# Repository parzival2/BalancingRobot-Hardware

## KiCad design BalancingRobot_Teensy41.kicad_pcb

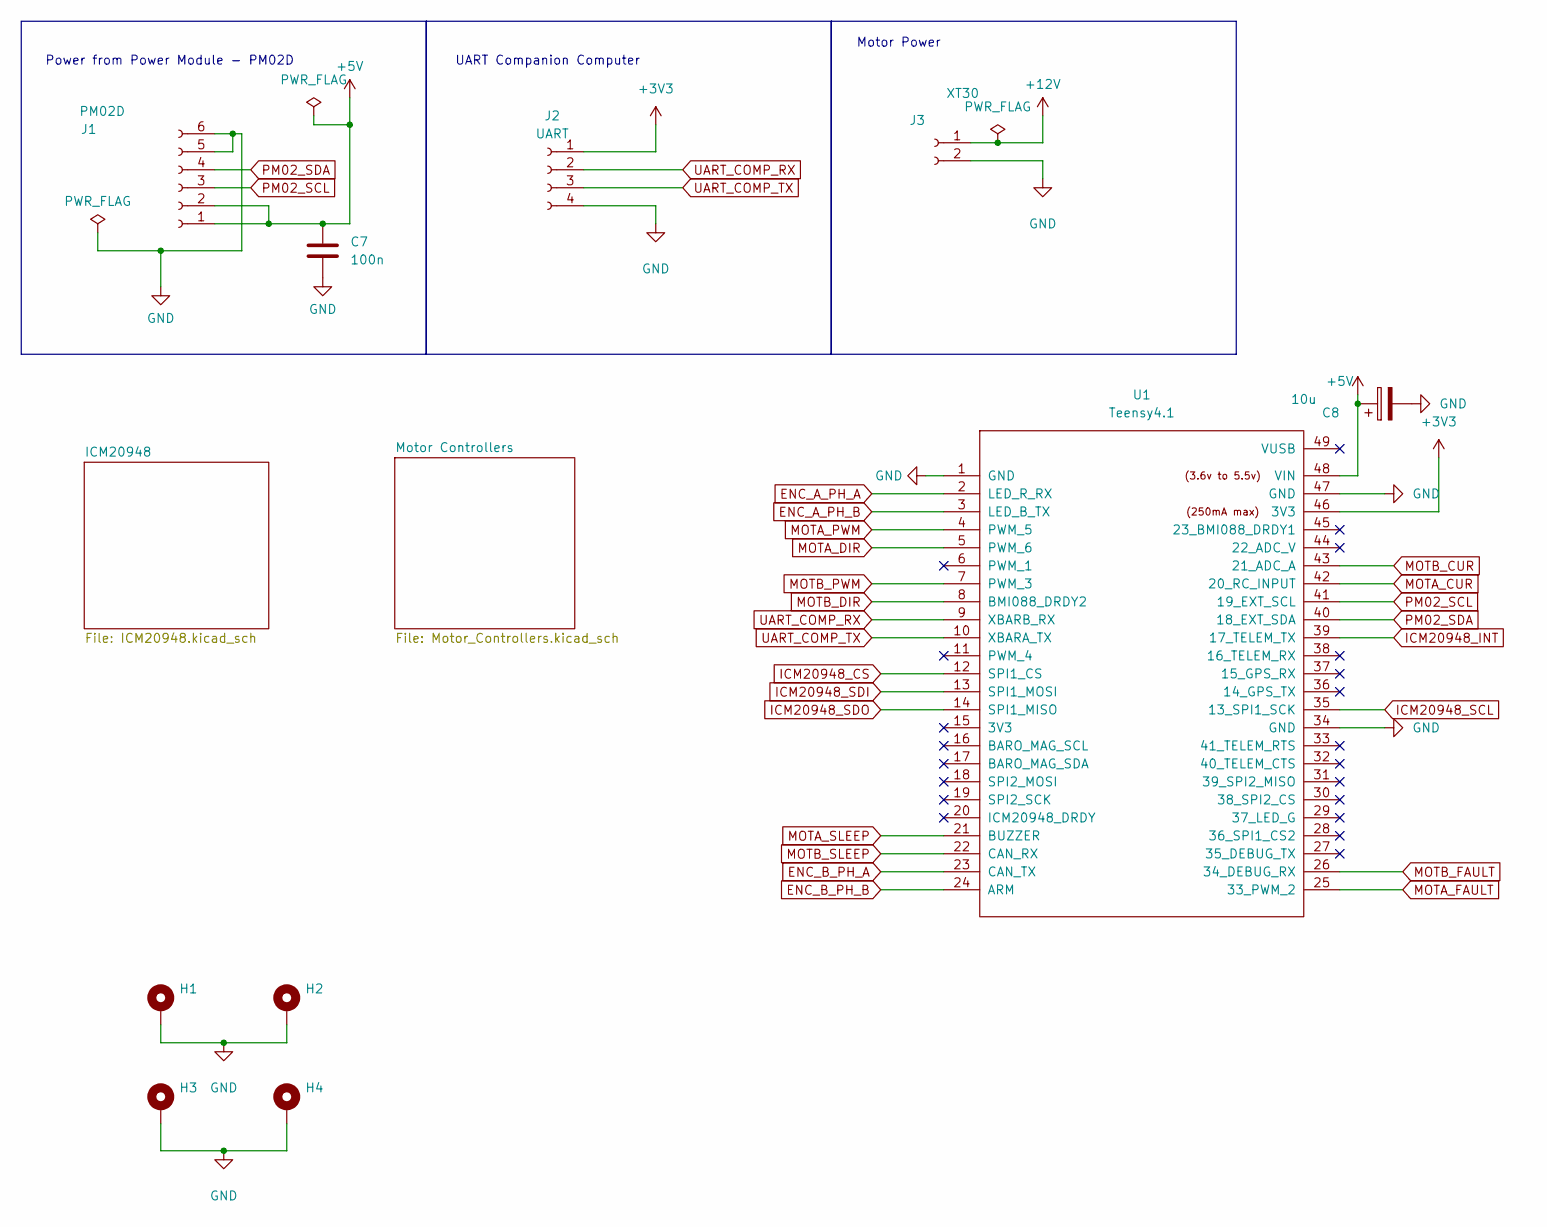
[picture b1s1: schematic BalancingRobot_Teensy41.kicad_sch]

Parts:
C7: 100n; C_Disc_D5.0mm_W2.5mm_P5.00mm
C8: 10u; CP_Radial_D5.0mm_P2.50mm
H1, H2, H3, H4: MountingHole_Pad; MountingHole_3.2mm_M3_Pad_Via
J1: PM02D; JST_PH_S6B-PH-K_1x06_P2.00mm_Horizontal
J2: UART; JST_PH_S4B-PH-K_1x04_P2.00mm_Horizontal
J3: XT30; AMASS_XT30U-F_1x02_P5.0mm_Vertical
U1: Teensy4.1; Teensy41

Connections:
+3V3: J2.1, U1.46 (3V3); also elsewhere on the board
+5V: C7.1, C8.1, J1.1, J1.2, U1.48 (VIN)
+12V: J3.1; also elsewhere on the board
ENC_A_PH_A: U1.2 (LED_R_RX); also elsewhere on the board
ENC_A_PH_B: U1.3 (LED_B_TX); also elsewhere on the board
ENC_B_PH_A: U1.23 (CAN_TX); also elsewhere on the board
ENC_B_PH_B: U1.24 (ARM); also elsewhere on the board
GND: C7.2, C8.2, H1.1, H2.1, H3.1, H4.1, J1.5, J1.6, J2.4, J3.2, U1.1 (GND), U1.34 (GND), U1.47 (GND); also elsewhere on the board
ICM20948_CS: U1.12 (SPI1_CS); also elsewhere on the board
ICM20948_INT: U1.39 (17_TELEM_TX); also elsewhere on the board
ICM20948_SCL: U1.35 (13_SPI1_SCK); also elsewhere on the board
ICM20948_SDI: U1.13 (SPI1_MOSI); also elsewhere on the board
ICM20948_SDO: U1.14 (SPI1_MISO); also elsewhere on the board
MOTA_CUR: U1.42 (20_RC_INPUT); also elsewhere on the board
MOTA_DIR: U1.5 (PWM_6); also elsewhere on the board
MOTA_FAULT: U1.25 (33_PWM_2); also elsewhere on the board
MOTA_PWM: U1.4 (PWM_5); also elsewhere on the board
MOTA_SLEEP: U1.21 (BUZZER); also elsewhere on the board
MOTB_CUR: U1.43 (21_ADC_A); also elsewhere on the board
MOTB_DIR: U1.8 (BMI088_DRDY2); also elsewhere on the board
MOTB_FAULT: U1.26 (34_DEBUG_RX); also elsewhere on the board
MOTB_PWM: U1.7 (PWM_3); also elsewhere on the board
MOTB_SLEEP: U1.22 (CAN_RX); also elsewhere on the board
PM02_SCL: J1.3, U1.41 (19_EXT_SCL)
PM02_SDA: J1.4, U1.40 (18_EXT_SDA)
UART_COMP_RX: J2.2, U1.9 (XBARB_RX)
UART_COMP_TX: J2.3, U1.10 (XBARA_TX)

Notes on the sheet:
Power from Power Module - PM02D
Motor Power
UART Companion Computer

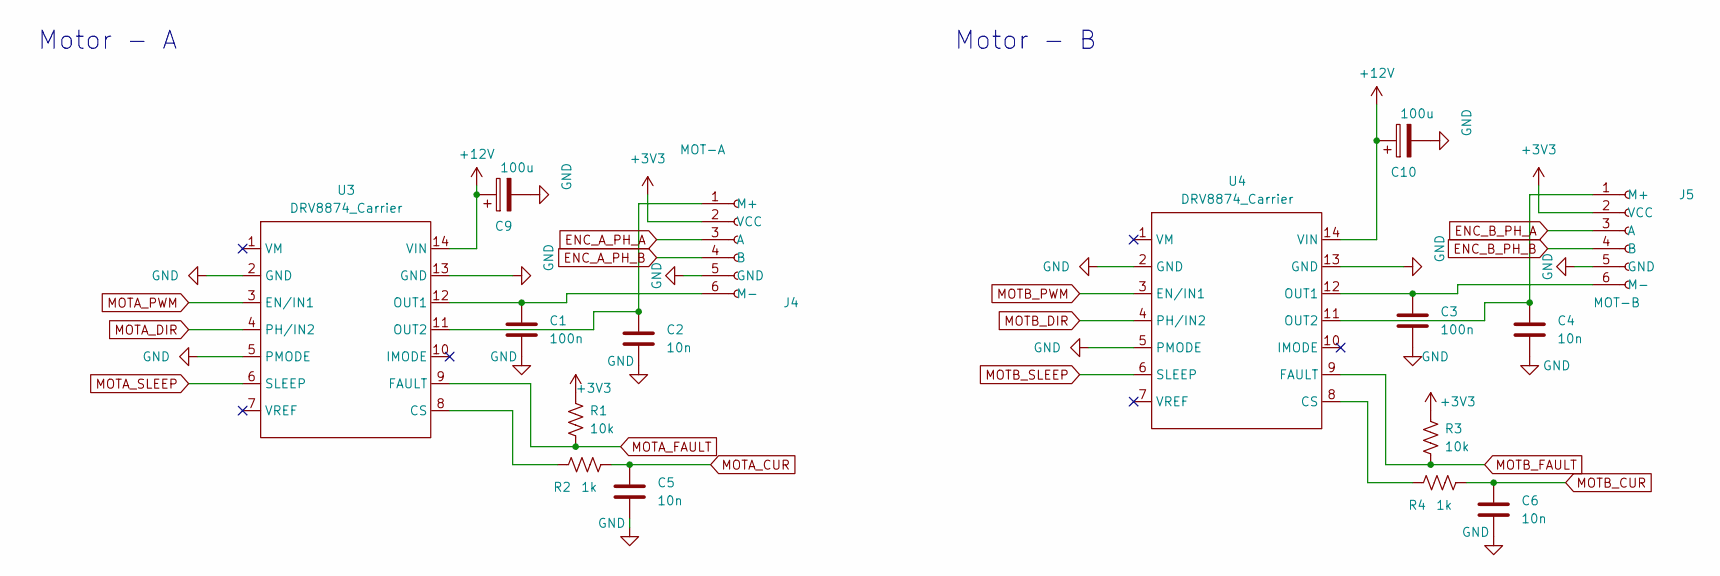
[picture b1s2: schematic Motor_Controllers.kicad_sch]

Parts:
C1, C3: 100n; C_Disc_D5.0mm_W2.5mm_P5.00mm
C2, C4, C5, C6: 10n; C_Disc_D5.0mm_W2.5mm_P5.00mm
C9, C10: 100u; CP_Radial_D5.0mm_P2.50mm
J4: MOT-A; JST_PH_S6B-PH-K_1x06_P2.00mm_Horizontal
J5: MOT-B; JST_PH_S6B-PH-K_1x06_P2.00mm_Horizontal
R1, R3: 10k; R_Axial_DIN0204_L3.6mm_D1.6mm_P7.62mm_Horizontal
R2, R4: 1k; R_Axial_DIN0204_L3.6mm_D1.6mm_P7.62mm_Horizontal
U3, U4: DRV8874_Carrier

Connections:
+3V3: J4.2 (VCC), J5.2 (VCC), R1.1, R3.1; also elsewhere on the board
+12V: C9.1, C10.1, U3.14 (VIN), U4.14 (VIN); also elsewhere on the board
ENC_A_PH_A: J4.3 (A); also elsewhere on the board
ENC_A_PH_B: J4.4 (B); also elsewhere on the board
ENC_B_PH_A: J5.3 (A); also elsewhere on the board
ENC_B_PH_B: J5.4 (B); also elsewhere on the board
GND: C1.2, C2.2, C3.2, C4.2, C5.2, C6.2, C9.2, C10.2, J4.5 (GND), J5.5 (GND), U3.2 (GND), U3.5 (PMODE), U3.13 (GND), U4.2 (GND), U4.5 (PMODE), U4.13 (GND); also elsewhere on the board
MOTA_CUR: C5.1, R2.2; also elsewhere on the board
MOTA_DIR: U3.4 (PH/IN2); also elsewhere on the board
MOTA_FAULT: R1.2, U3.9 (FAULT); also elsewhere on the board
MOTA_PWM: U3.3 (EN/IN1); also elsewhere on the board
MOTA_SLEEP: U3.6 (SLEEP); also elsewhere on the board
MOTB_CUR: C6.1, R4.2; also elsewhere on the board
MOTB_DIR: U4.4 (PH/IN2); also elsewhere on the board
MOTB_FAULT: R3.2, U4.9 (FAULT); also elsewhere on the board
MOTB_PWM: U4.3 (EN/IN1); also elsewhere on the board
MOTB_SLEEP: U4.6 (SLEEP); also elsewhere on the board
unnamed: C2.1, J4.1 (M+), U3.11 (OUT2)
unnamed: C1.1, J4.6 (M-), U3.12 (OUT1)
unnamed: C4.1, J5.1 (M+), U4.11 (OUT2)
unnamed: C3.1, J5.6 (M-), U4.12 (OUT1)
unnamed: R2.1, U3.8 (CS)
unnamed: R4.1, U4.8 (CS)

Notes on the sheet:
Motor - A
Motor - B

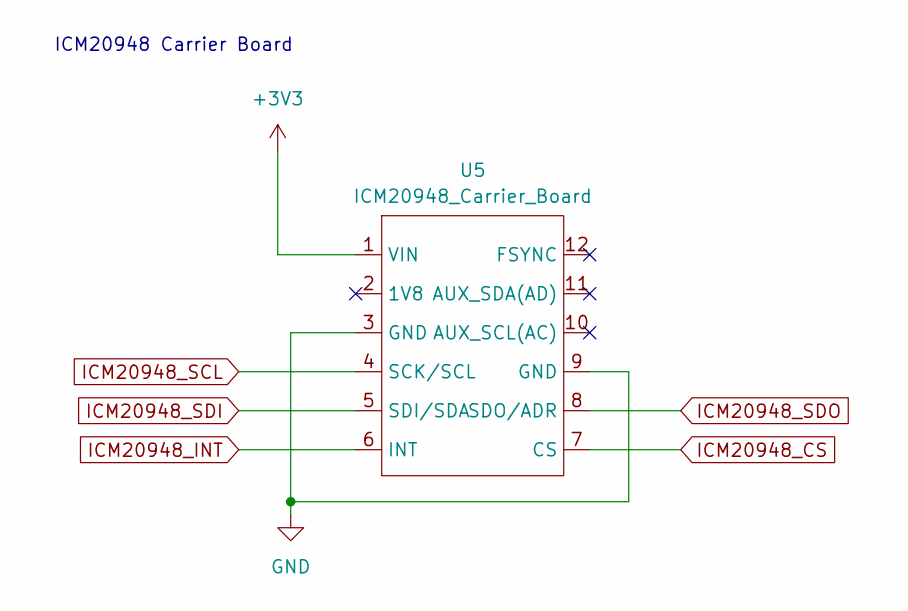
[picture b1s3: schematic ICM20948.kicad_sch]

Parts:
U5: ICM20948_Carrier_Board; ICM20948_Carrier

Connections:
+3V3: U5.1 (VIN); also elsewhere on the board
GND: U5.3 (GND), U5.9 (GND); also elsewhere on the board
ICM20948_CS: U5.7 (CS); also elsewhere on the board
ICM20948_INT: U5.6 (INT); also elsewhere on the board
ICM20948_SCL: U5.4 (SCK/SCL); also elsewhere on the board
ICM20948_SDI: U5.5 (SDI/SDA); also elsewhere on the board
ICM20948_SDO: U5.8 (SDO/ADR); also elsewhere on the board

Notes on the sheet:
ICM20948 Carrier Board

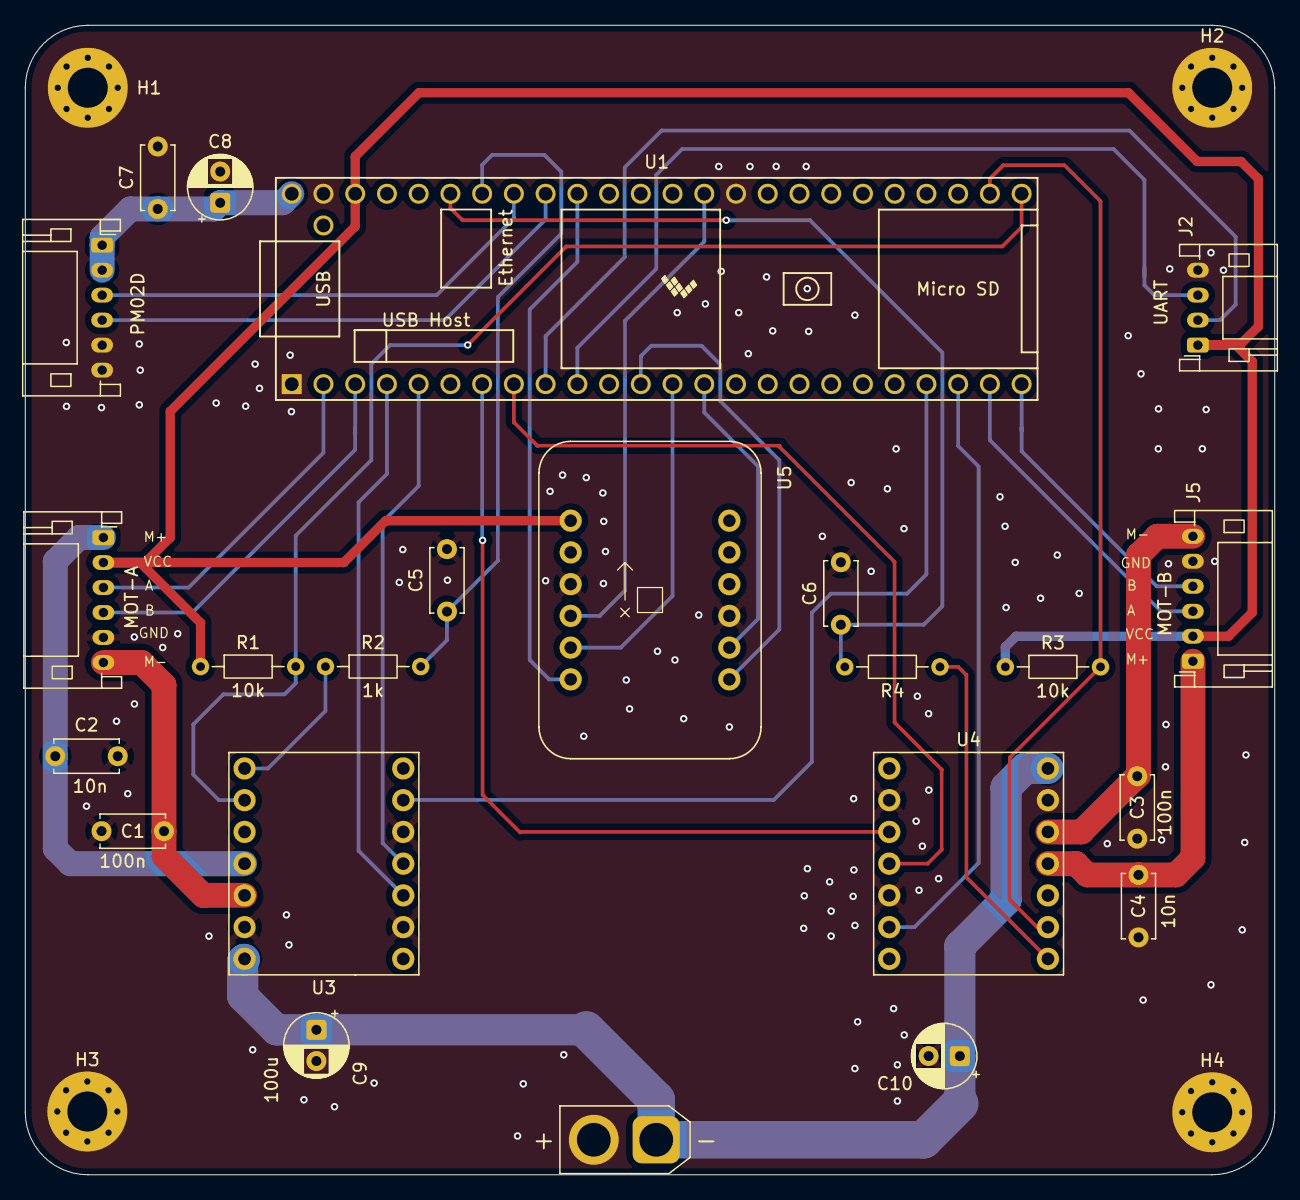
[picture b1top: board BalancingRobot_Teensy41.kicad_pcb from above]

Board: 2 copper layers, 100.0 x 92.0 mm, 27 parts (0 on the bottom side), 33 nets.

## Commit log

2026-03-29 Completed Schematic and the DRC also passes
2026-03-29 Added bulk caps for VIN on Teensy and Motor Controllers
2026-03-29 Split busy schematic into subpages. Mainly moved ICM20948 and the two motor controllers to inidividual pages
2026-03-30 Started with routing
2026-03-31 Fixed teensy library path
2026-04-01 Almost completed with routing
2026-05-14 Added some updates
